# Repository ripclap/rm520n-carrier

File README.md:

# RM520N Carrier

A six-layer carrier for the Quectel RM520N-GL, with 2.5 GbE, physical SIM and soldered eUICC, and an independent LoRa management controller.

**Revision A is a first-prototype release.** The layout is fully routed and the fabrication package is published. Supplier CAM acceptance, assembled-board testing, management firmware, and the remote LoRa network remain to be completed. See [validation status](docs/validation.md) before ordering.

| Front | Back |
| --- | --- |
|  |  |

These are CAD assembly renders. The installed modem and component bodies show the intended arrangement; they do not establish production fit or measured operation.

## Hardware

| Item | Revision A |
| --- | --- |
| PCB | 110 × 96 mm; six copper layers; nominal 1.6 mm; ENIG |
| Modem | M.2 Key B socket for RM520N-GL; modem purchased separately |
| Ethernet | RTL8125BG PCIe controller, separate magnetics, front-face RJ45 |
| Power input | Regulated 48 V ±5% passive PoE, or 12 V ±5% through J2 |
| Management | ESP32-S3FN8 on an independent always-on rail |
| Radio | E22-900MM22S SPI LoRa module; intended US 915 MHz network |
| SIM | Back-face nano-SIM at the left edge, viewed from the front; experimental ST4SIM-300M eUICC population |
| Service | USB-C service connection and controlled internal USB host ownership |
| Assembly | 423 fitted parts: 419 SMT and four through-hole |

The passive input **does not negotiate IEEE PoE, PoE+, or PoE++**. It shares system ground with the other interfaces and has no galvanically isolated power converter. Use the specified SELV supply/injector and verify its pinout, polarity, and voltage. J2 pin 1 is positive; pin 2 is ground.

The modem rail targets **3 A continuous at 0–40 °C**, subject to the measured efficiency, cooling, copper, ripple, and input-current requirements. Initial sustained 4 A qualification must start at or below 20 °C. Neither value is an established assembled-board rating. [Power requirements](manufacturing/rev-a/requirements/POWER_TARGETS_AND_RECOVERY.txt) define the acceptance limits.

The management rail stays powered during modem power cycling. Firmware is not included in this release. USB AT access, modem Ethernet operation, eUICC provisioning, and any SSH or console service depend on the exact modem firmware and need hardware verification. LoRa recovery and telemetry are planned software functions.

## Files and downloads

Use the [Rev A release](https://github.com/ripclap/rm520n-carrier/releases/tag/rev-a) for a fixed revision, or clone the repository:

```sh
git clone https://github.com/ripclap/rm520n-carrier.git
cd rm520n-carrier
git checkout rev-a
```

Open [hardware/rev-a/carrier.kicad_pro](hardware/rev-a/carrier.kicad_pro) in **KiCad 10**. The project includes its schematics, PCB, design rules, symbols, footprints, and model assets. Native KiCad files are the editable design source.

| Path | Contents |
| --- | --- |
| [hardware/rev-a/](hardware/rev-a/) | Authoritative schematics, PCB, rules, and local libraries |
| [hardware/assembly-preview/](hardware/assembly-preview/) | Presentation model with an installed modem; use the native Rev A PCB for fabrication |
| [manufacturing/rev-a/fabrication/](manufacturing/rev-a/fabrication/) | Six-layer Gerbers, drills, drill maps, and IPC-D-356 netlist |
| [manufacturing/rev-a/assembly/](manufacturing/rev-a/assembly/) | BOM, SMT and manual placements, and front/back drawings |
| [manufacturing/rev-a/requirements/](manufacturing/rev-a/requirements/) | Fabrication process, site schedules, power limits, and first-article procedure |
| [manufacturing/rev-a/verification/](manufacturing/rev-a/verification/) | Public-release checks and recorded dispositions |

Download the [BOM workbook](manufacturing/rev-a/assembly/RM520N-Carrier-RevA-BOM.xlsx) or [unpriced factory BOM](manufacturing/rev-a/assembly/Factory-BOM-unpriced.csv). The component model dated **2026-10-12** is **$101.60 per board at 25** or **$85.31 at 100**, excluding the Quectel, PCB fabrication, assembly, test, shipping, taxes, enclosure, antennas, and provisioning. Prices and availability require a new quote.

The [schematic PDF](docs/schematic.pdf) is available for review without KiCad. Verify a downloaded copy with `python3 tools/verify_release.py`; the [manifest](manifest.json) and [SHA256SUMS](SHA256SUMS) identify this release.

## Building a prototype

1. Read [fabrication and assembly](docs/fabrication.md) and obtain the fabricator's acceptance of the exact stack, impedance, drill, fill/cap, cover, and finished-metal requirements. This is not a generic six-layer order.
2. Send the complete fabrication, assembly, and requirement folders for the same revision. Include both SMT and manual through-hole placement files. Review every proposed substitution.
3. Inspect the received board and complete [bring-up](docs/bring-up.md) with a dummy load before installing the modem.
4. Record the tested hardware, modem firmware, power source, fixtures, and waveforms. Qualify the data interfaces, radio, SIM, enclosure, and recovery firmware before making a larger lot.

See [architecture](docs/architecture.md) for the power and management paths and [CONTRIBUTING.md](CONTRIBUTING.md) for design changes and test reports.

## License

Original hardware design files are licensed under **CERN-OHL-P-2.0**. Original documentation and renders are **CC-BY-4.0**; repository tools are **MIT**. Third-party libraries and assets retain their own licenses and notices. See [LICENSE](LICENSE) and [LICENSES/](LICENSES/).

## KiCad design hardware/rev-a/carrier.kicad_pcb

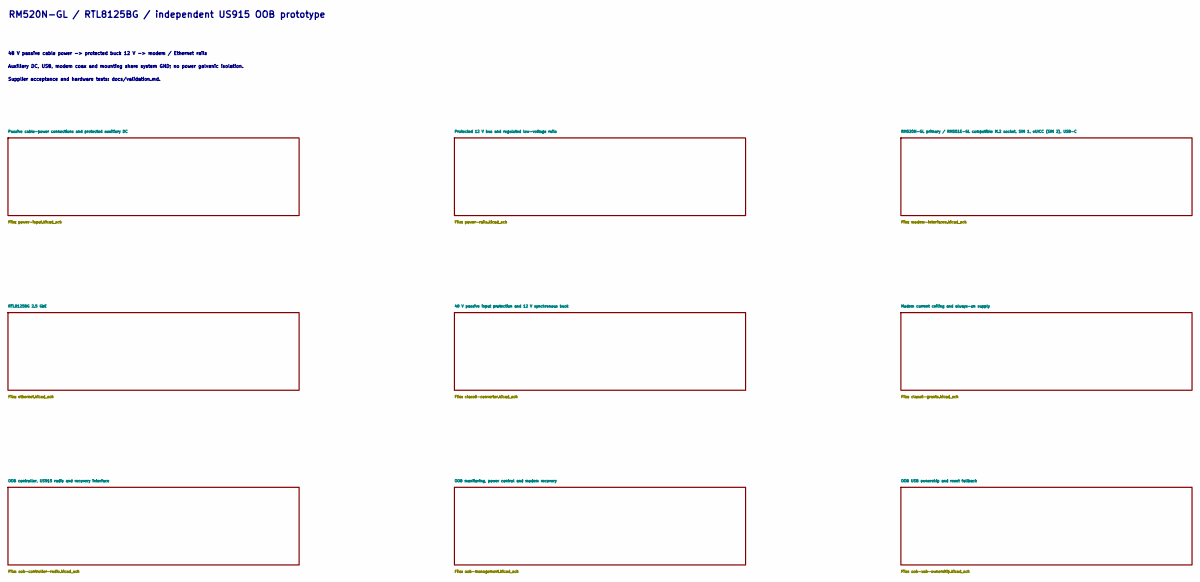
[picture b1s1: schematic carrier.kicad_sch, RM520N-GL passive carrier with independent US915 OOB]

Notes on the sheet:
RM520N-GL / RTL8125BG / independent US915 OOB prototype
48 V passive cable power -> protected buck 12 V -> modem / Ethernet rails
Auxiliary DC, USB, modem coax and mounting share system GND; no power galvanic isolation.
Supplier acceptance and hardware tests: docs/validation.md.

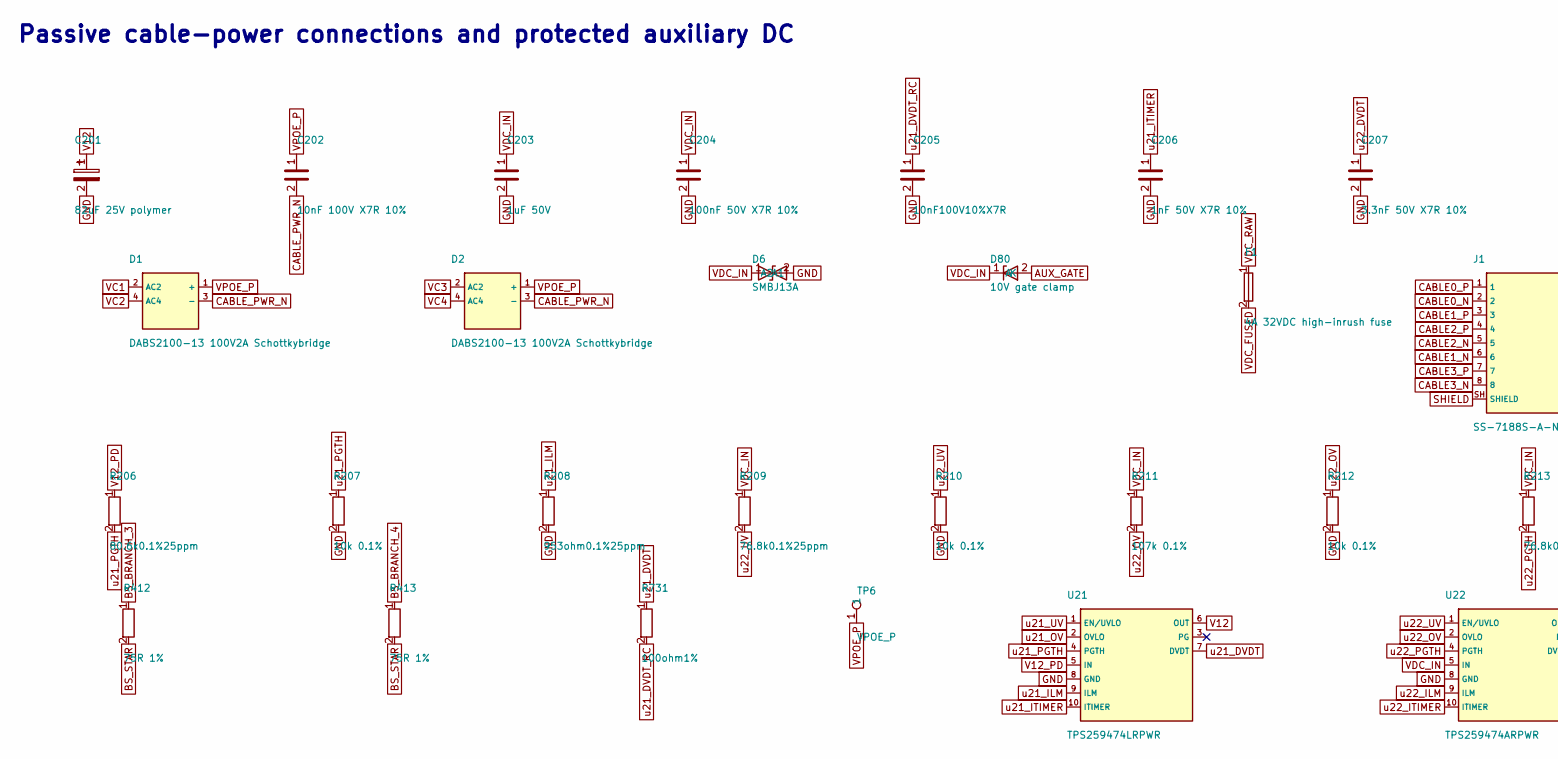
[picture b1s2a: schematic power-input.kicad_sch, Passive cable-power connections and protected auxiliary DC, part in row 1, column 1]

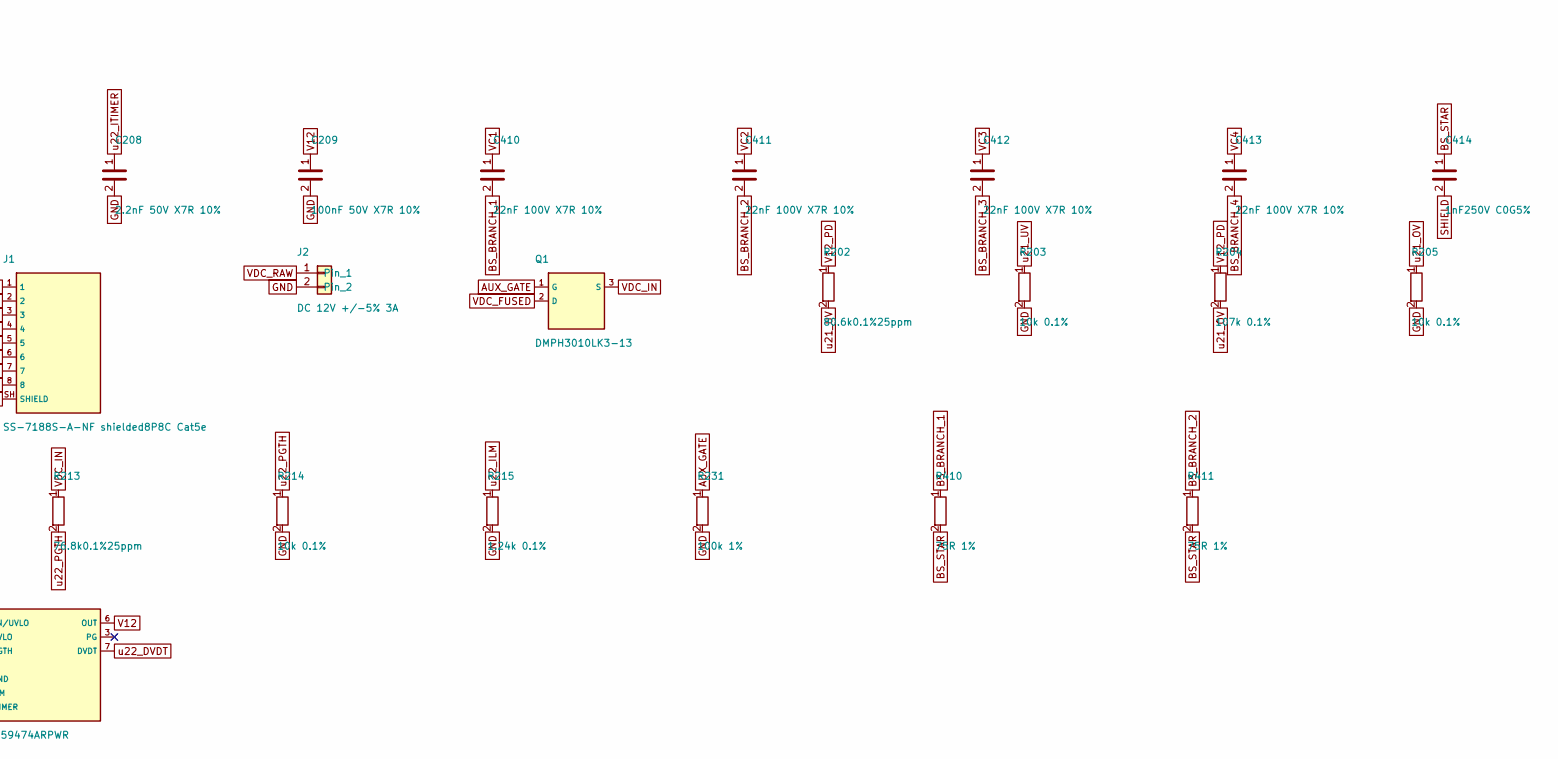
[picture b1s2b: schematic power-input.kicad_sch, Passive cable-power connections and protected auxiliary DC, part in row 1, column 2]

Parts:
C201: 82uF 25V polymer; CP_Elec_6.3x5.9; MPN 25SVPK82M
C202: 10nF 100V X7R 10%; C_0805_2012Metric; MPN C0805C103K1RACTU
C203: 1uF 50V; C_0805_2012Metric; MPN CL21B105KBFNNNF; LCSC C16195091
C204, C209: 100nF 50V X7R 10%; C_0402_1005Metric; MPN CL05B104KB5NNNC; LCSC C960916
C205: 10nF100V10%X7R; C_0805_2012Metric_DenseRevA_C205; MPN C0805C103K1RACTU
C206: 1nF 50V X7R 10%; C_0402_1005Metric; MPN C0402C102K5RACTU
C207: 3.3nF 50V X7R 10%; C_0402_1005Metric; MPN C0402C332K5RACTU
C208: 2.2nF 50V X7R 10%; C_0402_1005Metric; MPN C0402C222K5RACTU
C410, C411, C412, C413: 22nF 100V X7R 10%; C_0805_2012Metric; MPN C0805C223K1RACTU; LCSC C2178056
C414: 1nF250V C0G5%; C_0805_2012Metric; MPN C0805C102JAGACTU
D1, D2: DABS2100-13 100V2A Schottkybridge; Diodes_DABS2100_ABS_4_SMD; MPN DABS2100-13
D6: SMBJ13A; D_SMB; MPN SMBJ13A
D80: 10V gate clamp; D_SOD-123; MPN MMSZ5240B-7-F
F1: 4A 32VDC high-inrush fuse; AEM_F1206HI_1206; MPN F1206HI4000V032TM; LCSC C246771
J1: SS-7188S-A-NF shielded8P8C Cat5e; Stewart_SS_7188S_A_NF_ComponentSideCorrected; MPN SS-7188S-A-NF
J2: DC 12V +/-5% 3A; JST_XH_B2B-XH-A_1x02_P2.50mm_Vertical; MPN B2B-XH-A(LF)(SN)
Q1: DMPH3010LK3-13; Diodes_TO252_DMPH3010LK3; MPN DMPH3010LK3-13
R202: 80.6k0.1%25ppm; R_0402_1005Metric; MPN RT0402BRD0780K6L
R203, R205, R207, R210, R212, R214: 10k 0.1%; R_0402_1005Metric; MPN TNPW040210K0BEED
R204, R211: 107k 0.1%; R_0402_1005Metric; MPN RT0402BRD07107KL
R206: 80.6k0.1%25ppm; R_0402_1005Metric_DenseRevA_R206; MPN RT0402BRD0780K6L
R208: 953ohm0.1%25ppm; R_0603_1608Metric; MPN RT0603BRD07953RL
R209, R213: 76.8k0.1%25ppm; R_0402_1005Metric; MPN RT0402BRD0776K8L; LCSC C852913
R215: 1.24k 0.1%; R_0402_1005Metric; MPN TNPW04021K24BEED
R231: 100k 1%; R_0402_1005Metric; MPN CRCW0402100KFKED
R410, R411, R412, R413: 75R 1%; R_0805_2012Metric; MPN CRCW080575R0FKEA
R731: 100ohm1%; R_0402_1005Metric_DenseRevA_R731; MPN CRCW0402100RFKED
TP6: VPOE_P; TestPoint_Pad_D1.0mm
U21: TPS259474LRPWR; TI_RPW0010A_TPS25947; MPN TPS259474LRPWR
U22: TPS259474ARPWR; TI_RPW0010A_TPS25947; MPN TPS259474ARPWR

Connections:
AUX_GATE: D80.2 (A), Q1.1 (G), R231.1
BS_BRANCH_1: C410.2, R410.1
BS_BRANCH_2: C411.2, R411.1
BS_BRANCH_3: C412.2, R412.1
BS_BRANCH_4: C413.2, R413.1
BS_STAR: C414.1, R410.2, R411.2, R412.2, R413.2
CABLE0_N: J1.2; also elsewhere on the board
CABLE0_P: J1.1; also elsewhere on the board
CABLE1_N: J1.6; also elsewhere on the board
CABLE1_P: J1.3; also elsewhere on the board
CABLE2_N: J1.5; also elsewhere on the board
CABLE2_P: J1.4; also elsewhere on the board
CABLE3_N: J1.8; also elsewhere on the board
CABLE3_P: J1.7; also elsewhere on the board
CABLE_PWR_N: C202.2, D1.3 (-), D2.3 (-); also elsewhere on the board
GND: C201.2, C203.2, C204.2, C205.2, C206.2, C207.2, C208.2, C209.2, D6.2 (A2), J2.2, R203.2, R205.2, R207.2, R208.2, R210.2, R212.2, R214.2, R215.2, R231.2, U21.8 (GND), U22.8 (GND); also elsewhere on the board
SHIELD: C414.2, J1.SH (SHIELD); also elsewhere on the board
V12: C201.1, C209.1, U21.6 (OUT), U22.6 (OUT); also elsewhere on the board
V12_PD: R202.1, R204.1, R206.1, U21.5 (IN); also elsewhere on the board
VC1: C410.1, D1.2 (AC2); also elsewhere on the board
VC2: C411.1, D1.4 (AC4); also elsewhere on the board
VC3: C412.1, D2.2 (AC2); also elsewhere on the board
VC4: C413.1, D2.4 (AC4); also elsewhere on the board
VDC_FUSED: F1.2, Q1.2 (D)
VDC_IN: C203.1, C204.1, D6.1 (A1), D80.1 (K), Q1.3 (S), R209.1, R211.1, R213.1, U22.5 (IN); also elsewhere on the board
VDC_RAW: F1.1, J2.1
VPOE_P: C202.1, D1.1 (+), D2.1 (+), TP6.1 (1_1); also elsewhere on the board
u21_DVDT: R731.1, U21.7 (DVDT)
u21_DVDT_RC: C205.1, R731.2
u21_ILM: R208.1, U21.9 (ILM)
u21_ITIMER: C206.1, U21.10 (ITIMER)
u21_OV: R204.2, R205.1, U21.2 (OVLO)
u21_PGTH: R206.2, R207.1, U21.4 (PGTH)
u21_UV: R202.2, R203.1, U21.1 (EN/UVLO); also elsewhere on the board
u22_DVDT: C207.1, U22.7 (DVDT)
u22_ILM: R215.1, U22.9 (ILM)
u22_ITIMER: C208.1, U22.10 (ITIMER)
u22_OV: R211.2, R212.1, U22.2 (OVLO)
u22_PGTH: R213.2, R214.1, U22.4 (PGTH)
u22_UV: R209.2, R210.1, U22.1 (EN/UVLO)

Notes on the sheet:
Passive cable-power connections and protected auxiliary DC

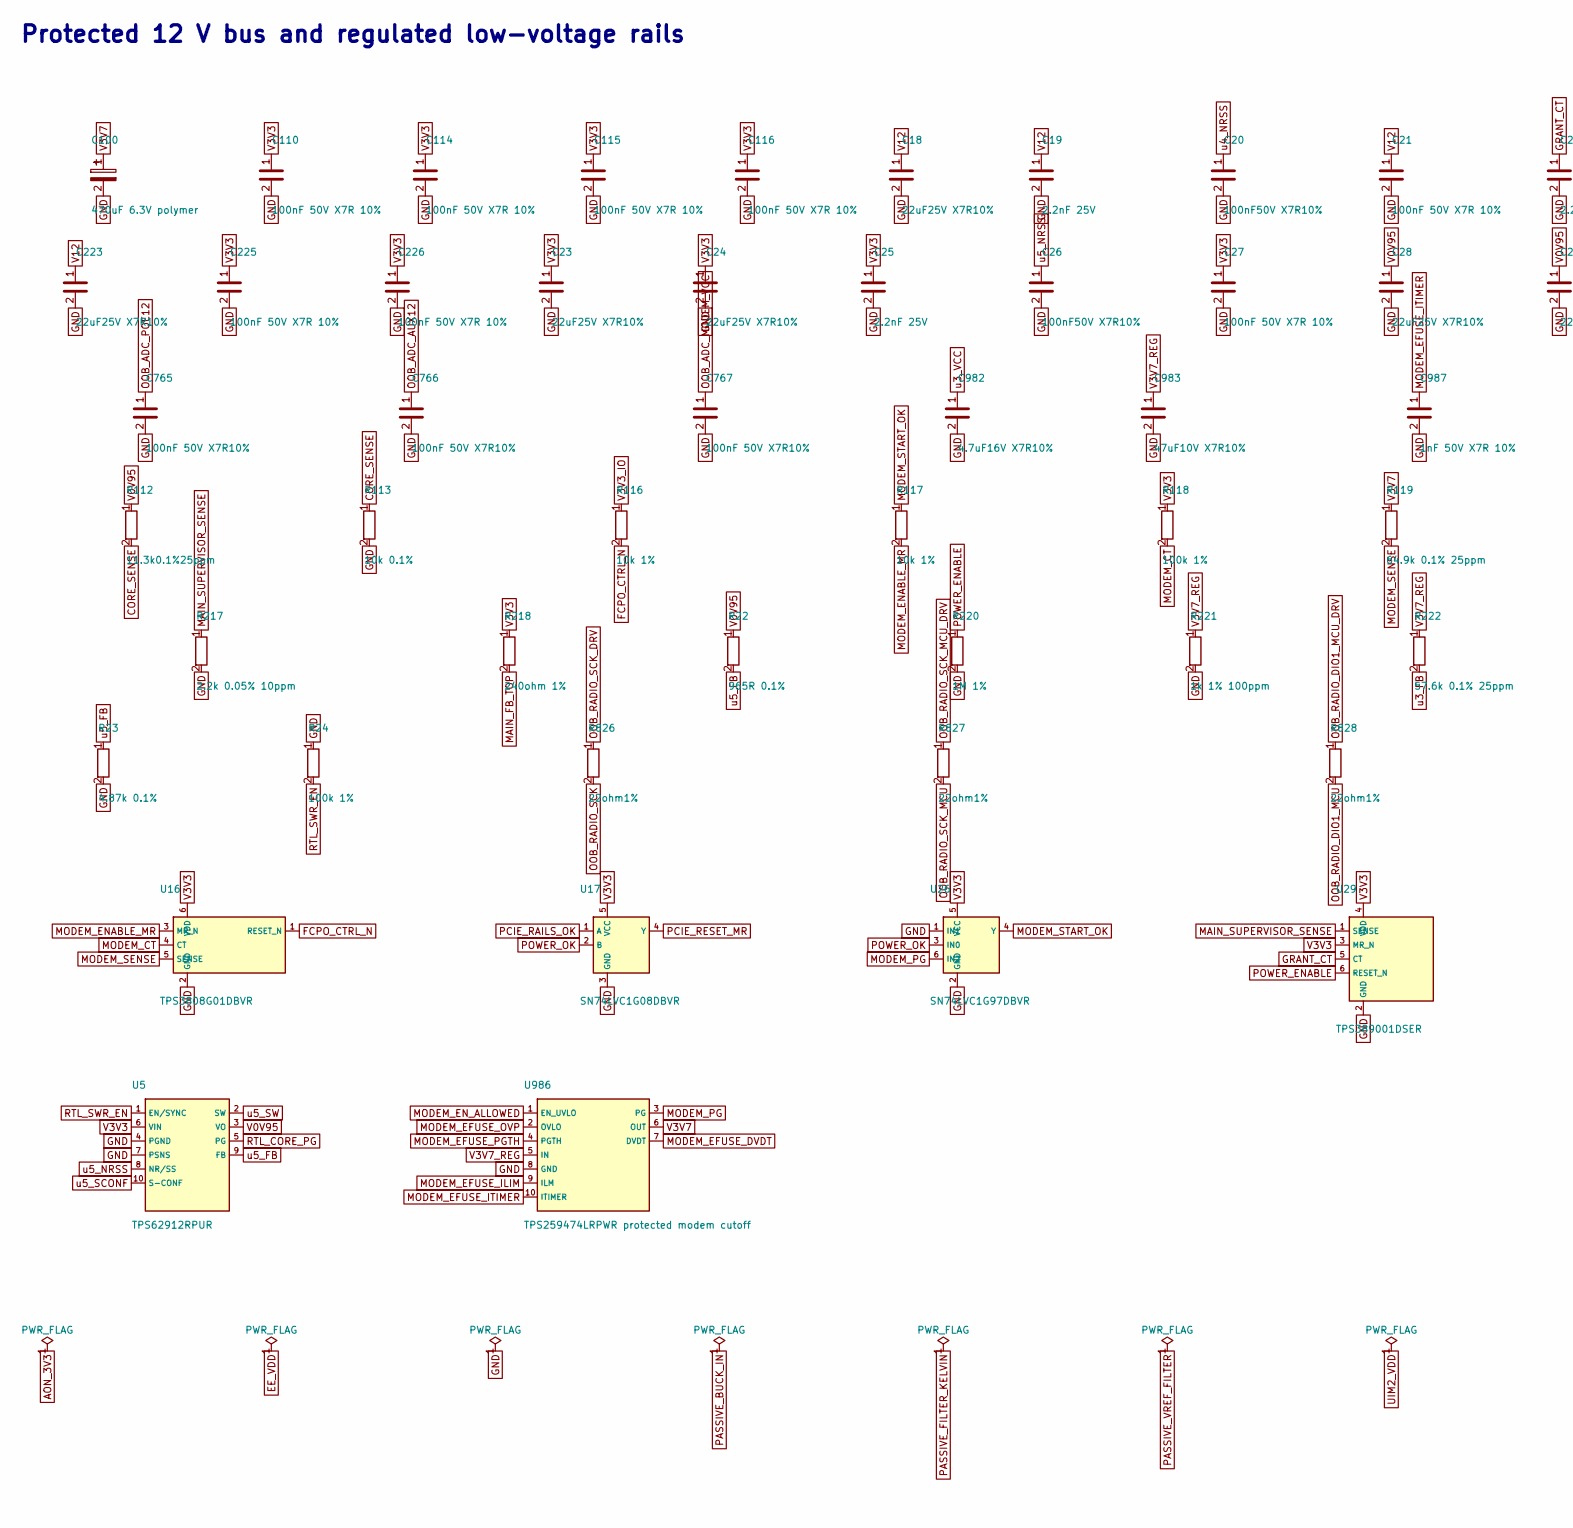
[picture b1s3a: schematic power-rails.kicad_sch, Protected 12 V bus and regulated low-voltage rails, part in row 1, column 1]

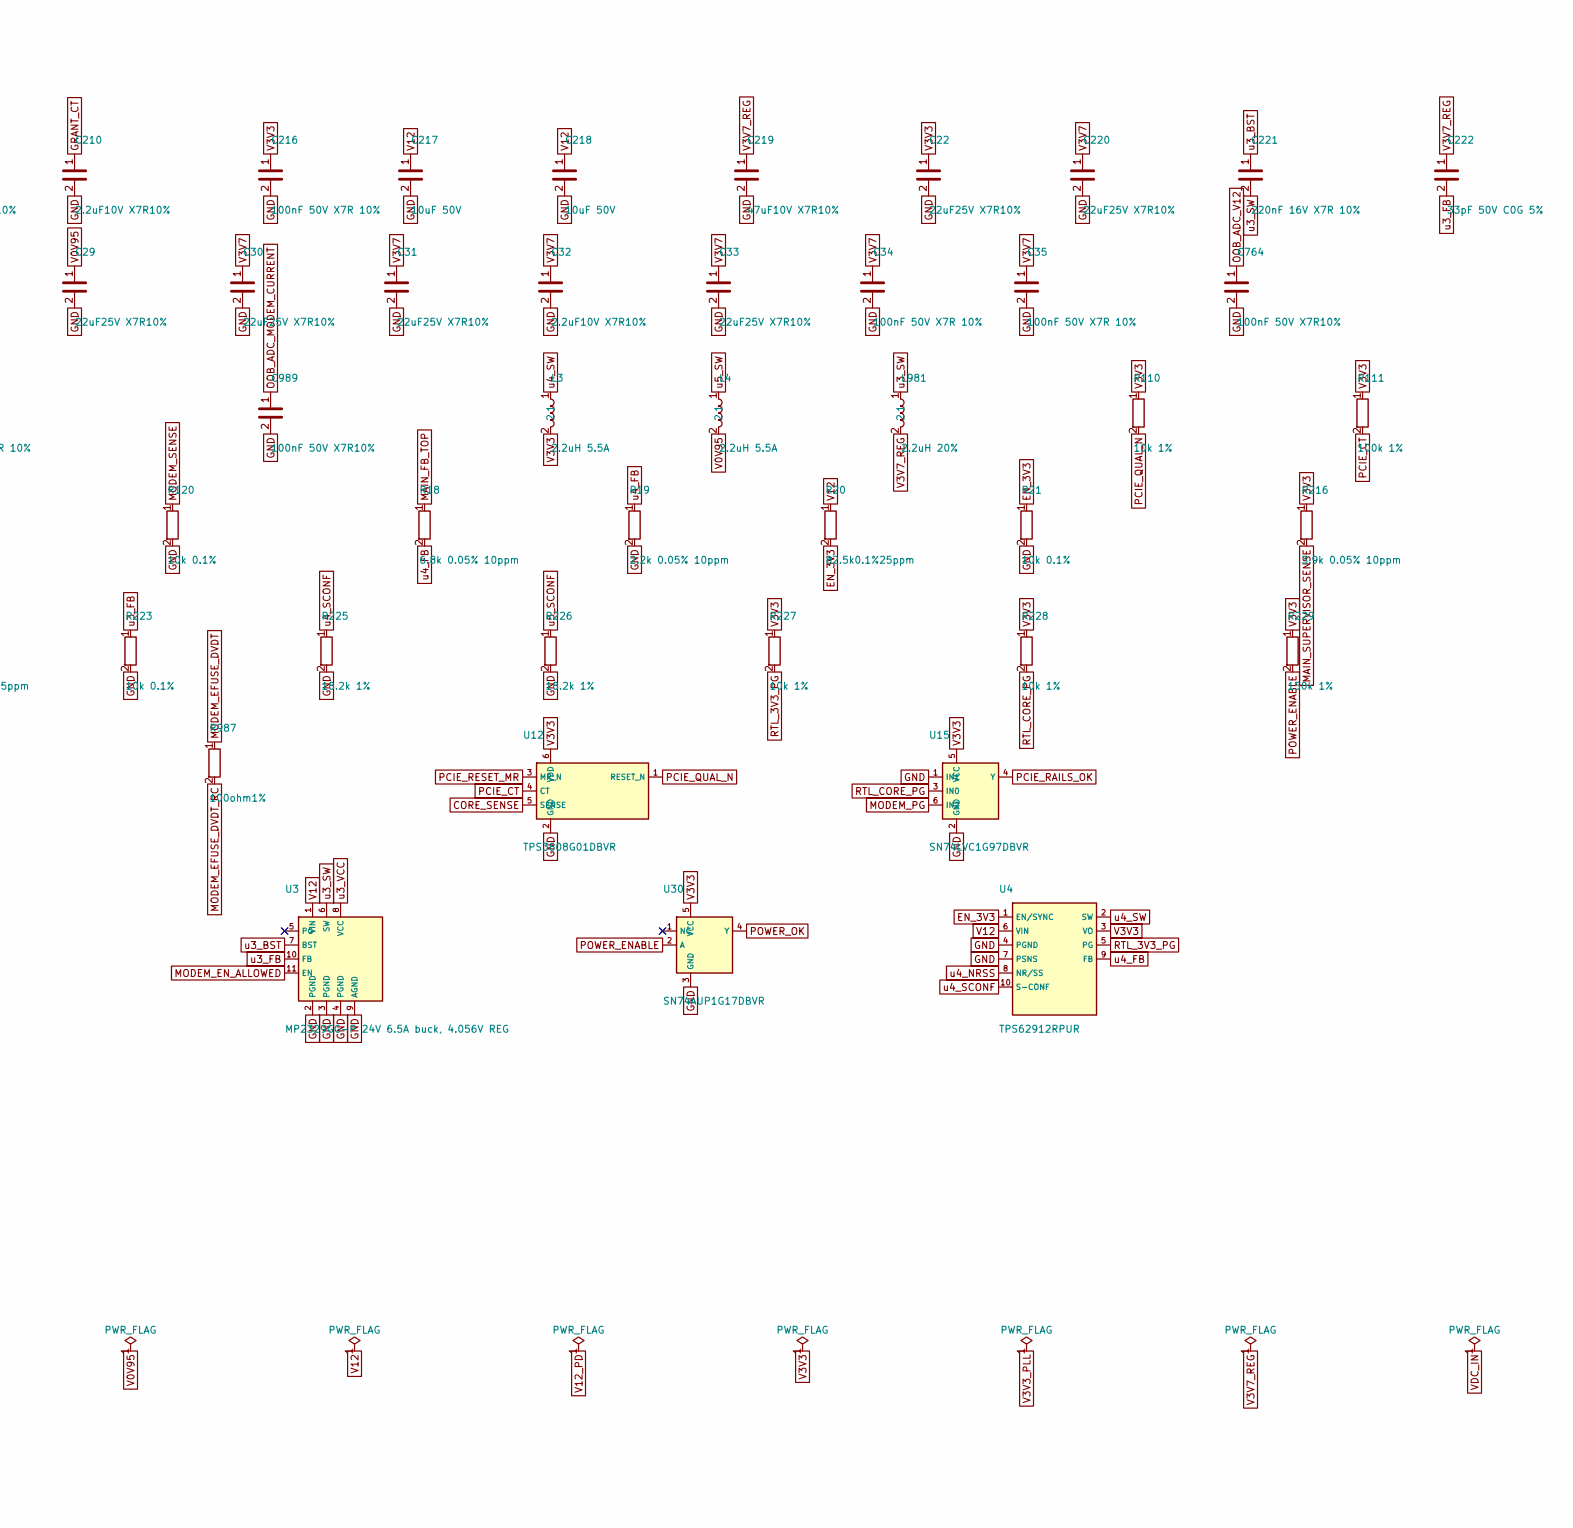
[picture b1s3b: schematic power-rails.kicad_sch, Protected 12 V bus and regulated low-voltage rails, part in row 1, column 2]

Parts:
C18, C22, C23, C24, C28, C29, C30, C31, C33, C220, C223: 22uF25V X7R10%; C_1210_3225Metric; MPN CL32B226KAJNNNE; LCSC C309062
C19, C25: 2.2nF 25V; C_0402_1005Metric; MPN GRM155R71E222KA01D
C20, C26: 100nF50V X7R10%; C_0402_1005Metric; MPN CL05B104KB5NNNC; LCSC C960916
C21, C27, C34, C35, C110, C114, C115, C116, C216, C225, C226: 100nF 50V X7R 10%; C_0402_1005Metric; MPN CL05B104KB5NNNC; LCSC C960916
C32, C210: 2.2uF10V X7R10%; C_0603_1608Metric; MPN CL10B225KP8NNNC; LCSC C100082
C100: 470uF 6.3V polymer; Nichicon_RHA_8x6.7_FPCAP; MPN RHA0J471MCN1GS
C217, C218: 10uF 50V; C_1210_3225Metric; MPN CL32B106KBJZW6E
C219: 47uF10V X7R10%; C_1210_3225Metric; MPN CL32B476KPJNNWE
C221: 220nF 16V X7R 10%; C_0603_1608Metric; MPN C0603C224K4RACTU
C222: 33pF 50V C0G 5%; C_0402_1005Metric; MPN C0402C330J5GACTU
C764, C765, C766, C767, C989: 100nF 50V X7R10%; C_0402_1005Metric; MPN CL05B104KB5NNNC; LCSC C960916
C982: 4.7uF16V X7R10%; C_0805_2012Metric; MPN C0805C475K4RACTU
C983: 47uF10V X7R10%; RevA_Dense100_50_C983; MPN CL32B476KPJNNWE
C987: 1nF 50V X7R 10%; C_0402_1005Metric; MPN C0402C102K5RACTU
L3, L4: 2.2uH 5.5A; L_Bourns_SRP5030T; MPN SRP5030TA-2R2M
L981: 2.2uH 20%; RevA_Dense100_50_L981; MPN SRP6030CA-2R2M
R18: 6.8k 0.05% 10ppm; R_0603_1608Metric; MPN RG1608N-682-W-T1
R19, R217: 2.2k 0.05% 10ppm; R_0603_1608Metric; MPN RG1608N-222-W-T1
R20: 82.5k0.1%25ppm; R_0402_1005Metric; MPN RT0402BRD0782K5L
R21, R113, R120, R223: 10k 0.1%; R_0402_1005Metric; MPN TNPW040210K0BEED
R22: 965R 0.1%; R_0402_1005Metric; MPN RN73R1ETTP9650B25
R23: 4.87k 0.1%; R_0402_1005Metric; MPN TNPW04024K87BEED
R24, R111, R118: 100k 1%; R_0402_1005Metric; MPN CRCW0402100KFKED
R110, R116, R117, R227, R228: 10k 1%; R_0402_1005Metric; MPN CRCW040210K0FKED
R112: 11.3k0.1%25ppm; R_0402_1005Metric; MPN RT0402BRD0711K3L
R119: 64.9k 0.1% 25ppm; R_0402_1005Metric; MPN RT0402BRD0764K9L; LCSC C852880
R216: 3.9k 0.05% 10ppm; R_0603_1608Metric; MPN RG1608N-392-W-T1
R218: 240ohm 1%; R_0402_1005Metric; MPN RC0402FR-07240RL
R220: 1M 1%; R_0402_1005Metric; MPN CRCW04021M00FKED
R221: 1k 1% 100ppm; R_0402_1005Metric; MPN CRCW04021K00FKED
R222: 57.6k 0.1% 25ppm; R_0402_1005Metric; MPN RT0402BRD0757K6L
R225, R226: 18.2k 1%; R_0402_1005Metric; MPN CRCW040218K2FKED
R229: 150k 1%; R_0402_1005Metric; MPN CRCW0402150KFKED
R826: 22ohm1%; RevA_DensePrimary100_PIN50_R826; MPN CRCW040222R0FKED
R827, R828: 22ohm1%; R_0402_1005Metric; MPN CRCW040222R0FKED
R987: 100ohm1%; RevA_Dense100_50_R987; MPN CRCW0402100RFKED
U3: MP2329GG-P 24V 6.5A buck, 4.056V REG; MPS_MP2386_QFN11_2x2; MPN MP2329GG-P
U4, U5: TPS62912RPUR; TI_RPU0010A_TPS62912; MPN TPS62912RPUR
U12, U16: TPS3808G01DBVR; SOT-23-6; MPN TPS3808G01DBVR
U15, U26: SN74LVC1G97DBVR; SOT-23-6; MPN SN74LVC1G97DBVR
U17: SN74LVC1G08DBVR; SOT-23-5; MPN SN74LVC1G08DBVR
U29: TPS389001DSER; TI_DSE6_TPS3890_1p5x1p5_Manufacturer; MPN TPS389001DSER
U30: SN74AUP1G17DBVR; SOT-23-5; MPN SN74AUP1G17DBVR
U986: TPS259474LRPWR protected modem cutoff; TI_RPW0010A_TPS25947; MPN TPS259474LRPWR

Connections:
CORE_SENSE: R112.2, R113.1, U12.5 (SENSE)
EN_3V3: R20.2, R21.1, U4.1 (EN/SYNC)
FCPO_CTRL_N: R116.2, U16.1 (RESET_N); also elsewhere on the board
GND: C18.2, C19.2, C20.2, C21.2, C22.2, C23.2, C24.2, C25.2, C26.2, C27.2, C28.2, C29.2, C30.2, C31.2, C32.2, C33.2, C34.2, C35.2, C100.2, C110.2, C114.2, C115.2, C116.2, C210.2, C216.2, C217.2, C218.2, C219.2, C220.2, C223.2, C225.2, C226.2, C764.2, C765.2, C766.2, C767.2, C982.2, C983.2, C987.2, C989.2, R19.2, R21.2, R23.2, R24.1, R113.2, R120.2, R217.2, R220.2, R221.2, R223.2, R225.2, R226.2, U3.2 (PGND), U3.3 (PGND), U3.4 (PGND), U3.9 (AGND), U4.4 (PGND), U4.7 (PSNS), U5.4 (PGND), U5.7 (PSNS), U12.2 (GND), U15.1 (IN1), U15.2 (GND), U16.2 (GND), U17.3 (GND), U26.1 (IN1), U26.2 (GND), U29.2 (GND), U30.3 (GND), U986.8 (GND); also elsewhere on the board
GRANT_CT: C210.1, U29.5 (CT)
MAIN_FB_TOP: R18.1, R218.2
MAIN_SUPERVISOR_SENSE: R216.2, R217.1, U29.1 (SENSE)
MODEM_CT: R118.2, U16.4 (CT)
MODEM_EFUSE_DVDT: R987.1, U986.7 (DVDT)
MODEM_EFUSE_DVDT_RC: R987.2; also elsewhere on the board
MODEM_EFUSE_ILIM: U986.9 (ILM); also elsewhere on the board
MODEM_EFUSE_ITIMER: C987.1, U986.10 (ITIMER)
MODEM_EFUSE_OVP: U986.2 (OVLO); also elsewhere on the board
MODEM_EFUSE_PGTH: U986.4 (PGTH); also elsewhere on the board
MODEM_ENABLE_MR: R117.2, U16.3 (MR_N); also elsewhere on the board
MODEM_EN_ALLOWED: U3.11 (EN), U986.1 (EN_UVLO); also elsewhere on the board
MODEM_PG: U15.6 (IN2), U26.6 (IN2), U986.3 (PG); also elsewhere on the board
MODEM_SENSE: R119.2, R120.1, U16.5 (SENSE)
MODEM_START_OK: R117.1, U26.4 (Y); also elsewhere on the board
OOB_ADC_AUX12: C766.1; also elsewhere on the board
OOB_ADC_MODEM_CURRENT: C989.1; also elsewhere on the board
OOB_ADC_MODEM_VCC: C767.1; also elsewhere on the board
OOB_ADC_POE12: C765.1; also elsewhere on the board
OOB_ADC_V12: C764.1; also elsewhere on the board
OOB_RADIO_DIO1_MCU: R828.2; also elsewhere on the board
OOB_RADIO_DIO1_MCU_DRV: R828.1; also elsewhere on the board
OOB_RADIO_SCK: R826.2; also elsewhere on the board
OOB_RADIO_SCK_DRV: R826.1; also elsewhere on the board
OOB_RADIO_SCK_MCU: R827.2; also elsewhere on the board
OOB_RADIO_SCK_MCU_DRV: R827.1; also elsewhere on the board
PCIE_CT: R111.2, U12.4 (CT)
PCIE_QUAL_N: R110.2, U12.1 (RESET_N); also elsewhere on the board
PCIE_RAILS_OK: U15.4 (Y), U17.1 (A)
PCIE_RESET_MR: U12.3 (MR_N), U17.4 (Y)
POWER_ENABLE: R220.1, R229.2, U29.6 (RESET_N), U30.2 (A)
POWER_OK: U17.2 (B), U26.3 (IN0), U30.4 (Y); also elsewhere on the board
RTL_3V3_PG: R227.2, U4.5 (PG)
RTL_CORE_PG: R228.2, U5.5 (PG), U15.3 (IN0)
RTL_SWR_EN: R24.2, U5.1 (EN/SYNC); also elsewhere on the board
V0V95: C28.1, C29.1, L4.2, R22.1, R112.1, U5.3 (VO); also elsewhere on the board
V3V3: C22.1, C23.1, C24.1, C25.1, C27.1, C110.1, C114.1, C115.1, C116.1, C216.1, C225.1, C226.1, L3.2, R110.1, R111.1, R118.1, R216.1, R218.1, R227.1, R228.1, R229.1, U4.3 (VO), U5.6 (VIN), U12.6 (VDD), U15.5 (VCC), U16.6 (VDD), U17.5 (VCC), U26.5 (VCC), U29.3 (MR_N), U29.4 (VDD), U30.5 (VCC); also elsewhere on the board
V3V3_IO: R116.1; also elsewhere on the board
V3V7: C30.1, C31.1, C32.1, C33.1, C34.1, C35.1, C100.1, C220.1, R119.1, U986.6 (OUT); also elsewhere on the board
V3V7_REG: C219.1, C222.1, C983.1, L981.2, R221.1, R222.1, U986.5 (IN); also elsewhere on the board
V12: C18.1, C19.1, C21.1, C217.1, C218.1, C223.1, R20.1, U3.1 (VIN), U4.6 (VIN); also elsewhere on the board
u3_BST: C221.1, U3.7 (BST)
u3_FB: C222.2, R222.2, R223.1, U3.10 (FB)
u3_SW: C221.2, L981.1, U3.6 (SW)
u3_VCC: C982.1, U3.8 (VCC)
u4_FB: R18.2, R19.1, U4.9 (FB)
u4_NRSS: C20.1, U4.8 (NR/SS)
u4_SCONF: R225.1, U4.10 (S-CONF)
u4_SW: L3.1, U4.2 (SW)
u5_FB: R22.2, R23.1, U5.9 (FB)
u5_NRSS: C26.1, U5.8 (NR/SS)
u5_SCONF: R226.1, U5.10 (S-CONF)
u5_SW: L4.1, U5.2 (SW)

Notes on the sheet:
Protected 12 V bus and regulated low-voltage rails
